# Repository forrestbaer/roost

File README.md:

## Roost keyboard

Based off the Sweep v2.1, added 2mm or so horizontal space, added another set of keys and slots for a fat power switch. Moved battery connectors to the board, moved reset switch so it's easier to get to without being in the way. Larger holes are for mounting these: Mouser part: 575-7305015154727100 for pluggable switches.

Recently added v2 gerbers which use normal Kalih choc hot pluggable sockets as they're MUCH easier and more reliable to solder than the plugs.. Also did a few routing changes but it's otherwise the same board, same config.

Feel free to copy and modify..

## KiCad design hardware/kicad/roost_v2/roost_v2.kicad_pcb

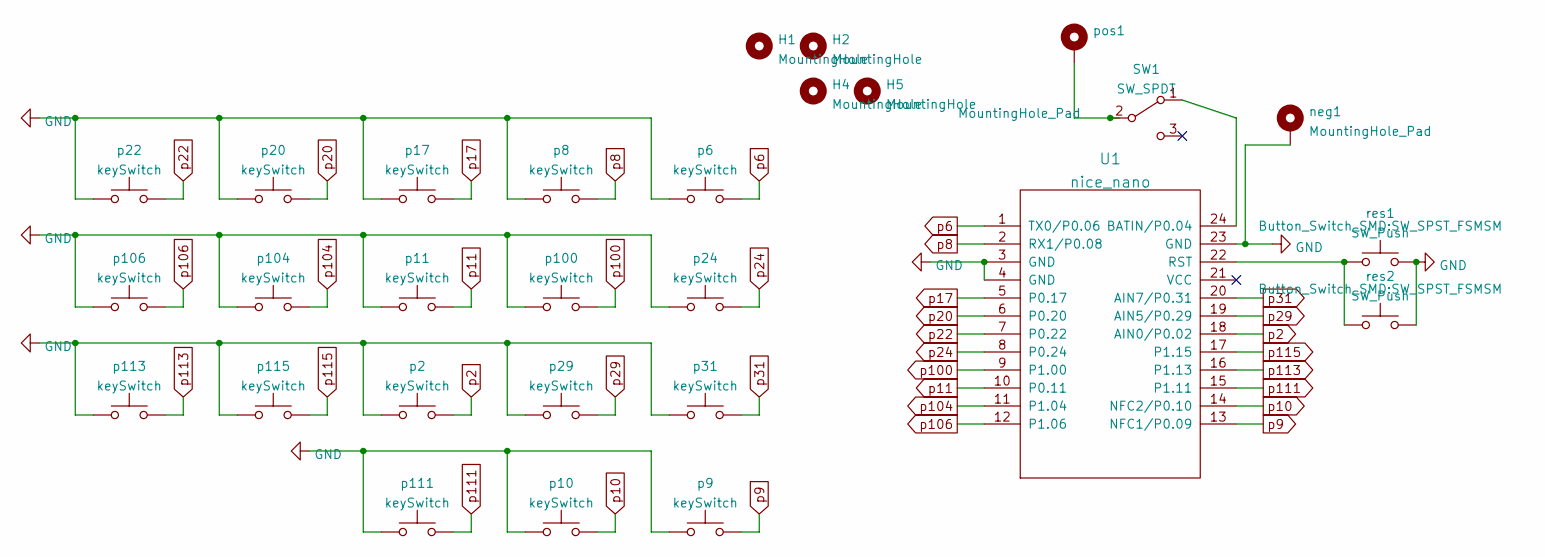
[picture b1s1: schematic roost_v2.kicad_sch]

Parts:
H1, H2, H4, H5: MountingHole; MountingHole_2.2mm_M2
SW1: SW_SPDT; bigswitch
U1: nice_nano
neg1: MountingHole_Pad; MountingHole_2.2mm_M2_DIN965_Pad
p2, p6, p8, p9, p10, p11, p17, p20, p22, p24, p29, p31, p100, p104, p106, p111, p113, p115: keySwitch; Kailh_socket_PG1350_reversible
pos1: MountingHole_Pad; MountingHole_2.2mm_M2_DIN965_Pad
res1, res2: SW_Push; SW_SPST_FSMSM

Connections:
GND: U1.3 (GND), U1.4 (GND), U1.23 (GND), neg1.1, p2.1, p6.1, p8.1, p9.1, p10.1, p11.1, p17.1, p20.1, p22.1, p24.1, p29.1, p31.1, p100.1, p104.1, p106.1, p111.1, p113.1, p115.1, res1.2, res2.2; also elsewhere on the board
unnamed: SW1.1 (A), U1.24 (BATIN/P0.04)
unnamed 2: SW1.2 (B), pos1.1; also elsewhere on the board
unnamed: U1.22 (RST), res1.1, res2.1
p2: U1.18 (AIN0/P0.02), p2.2
p6: U1.1 (TX0/P0.06), p6.2
p8: U1.2 (RX1/P0.08), p8.2
p9: U1.13 (NFC1/P0.09), p9.2
p10: U1.14 (NFC2/P0.10), p10.2
p11: U1.10 (P0.11), p11.2
p17: U1.5 (P0.17), p17.2
p20: U1.6 (P0.20), p20.2
p22: U1.7 (P0.22), p22.2
p24: U1.8 (P0.24), p24.2
p29: U1.19 (AIN5/P0.29), p29.2
p31: U1.20 (AIN7/P0.31), p31.2
p100: U1.9 (P1.00), p100.2
p104: U1.11 (P1.04), p104.2
p106: U1.12 (P1.06), p106.2
p111: U1.15 (P1.11), p111.2
p113: U1.16 (P1.13), p113.2
p115: U1.17 (P1.15), p115.2

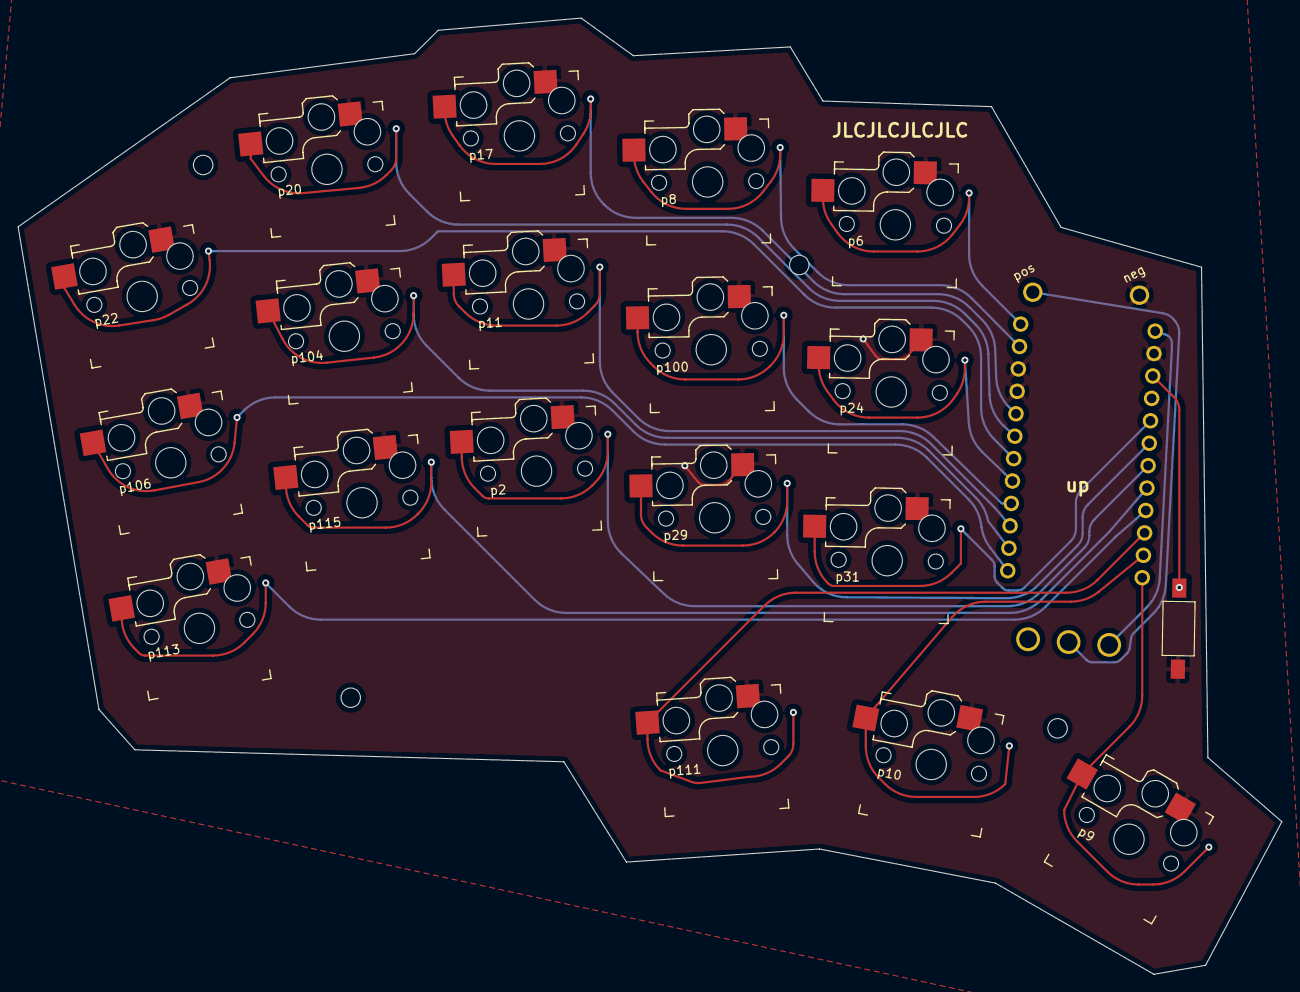
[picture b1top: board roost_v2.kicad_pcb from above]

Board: 2 copper layers, 143.0 x 108.2 mm, 28 parts (1 on the bottom side), 22 nets.

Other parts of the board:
neg: MountingHole_Pad; MountingHole_2.2mm_M2_DIN965_Pad
pos: MountingHole_Pad; MountingHole_2.2mm_M2_DIN965_Pad

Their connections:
GND: neg.1; also elsewhere on the board
unnamed 2: pos.1; also elsewhere on the board

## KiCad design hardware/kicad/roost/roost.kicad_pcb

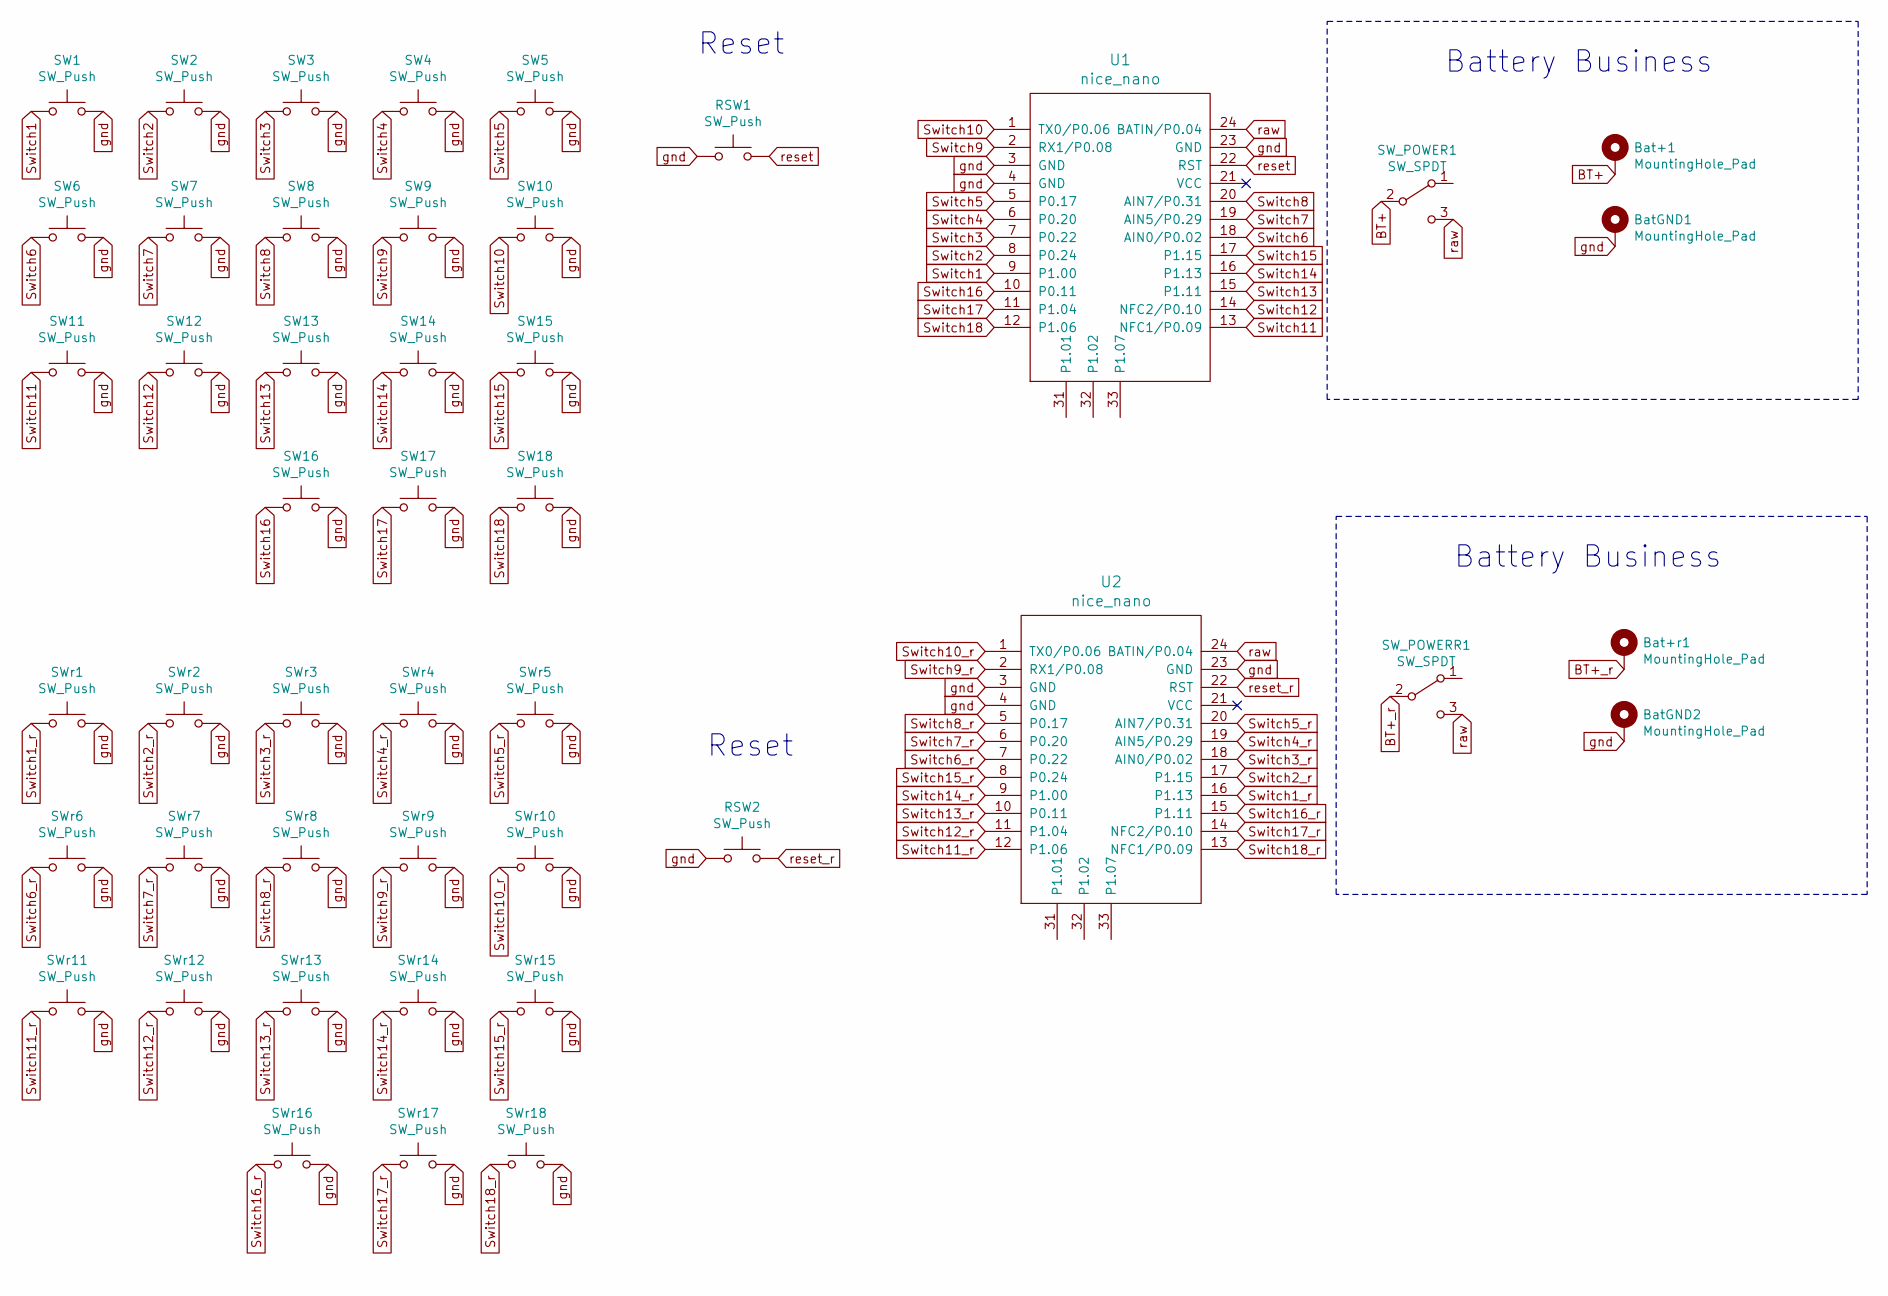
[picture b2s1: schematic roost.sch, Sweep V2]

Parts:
Bat+1: MountingHole_Pad; battery hole
Bat+r1: MountingHole_Pad; battery hole
BatGND1, BatGND2: MountingHole_Pad; battery hole
RSW1, RSW2: SW_Push; SW_SPST_B3U-1000P
SW1, SW2, SW3, SW4, SW5, SW6, SW7, SW8, SW9, SW10, SW11, SW12, SW13, SW14, SW15, SW16, SW17, SW18: SW_Push; SW_Kailh_Choc_V1_1.00u
SW_POWER1: SW_SPDT; bigswitch
SW_POWERR1: SW_SPDT; bigswitch
SWr1, SWr2, SWr3, SWr4, SWr5, SWr6, SWr7, SWr8, SWr9, SWr10, SWr11, SWr12, SWr13, SWr14, SWr15, SWr16, SWr17, SWr18: SW_Push; SW_Kailh_Choc_V1_1.00u
U1, U2: nice_nano

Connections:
BT+: Bat+1.1, SW_POWER1.2 (B); also elsewhere on the board
BT+_r: Bat+r1.1, SW_POWERR1.2 (B); also elsewhere on the board
Switch1: SW1.1, U1.9 (P1.00)
Switch1_r: SWr1.1, U2.16 (P1.13)
Switch2: SW2.1, U1.8 (P0.24)
Switch2_r: SWr2.1, U2.17 (P1.15)
Switch3: SW3.1, U1.7 (P0.22)
Switch3_r: SWr3.1, U2.18 (AIN0/P0.02)
Switch4: SW4.1, U1.6 (P0.20)
Switch4_r: SWr4.1, U2.19 (AIN5/P0.29)
Switch5: SW5.1, U1.5 (P0.17)
Switch5_r: SWr5.1, U2.20 (AIN7/P0.31)
Switch6: SW6.1, U1.18 (AIN0/P0.02)
Switch6_r: SWr6.1, U2.7 (P0.22)
Switch7: SW7.1, U1.19 (AIN5/P0.29)
Switch7_r: SWr7.1, U2.6 (P0.20)
Switch8: SW8.1, U1.20 (AIN7/P0.31)
Switch8_r: SWr8.1, U2.5 (P0.17)
Switch9: SW9.1, U1.2 (RX1/P0.08)
Switch9_r: SWr9.1, U2.2 (RX1/P0.08)
Switch10: SW10.1, U1.1 (TX0/P0.06)
Switch10_r: SWr10.1, U2.1 (TX0/P0.06)
Switch11: SW11.1, U1.13 (NFC1/P0.09)
Switch11_r: SWr11.1, U2.12 (P1.06)
Switch12: SW12.1, U1.14 (NFC2/P0.10)
Switch12_r: SWr12.1, U2.11 (P1.04)
Switch13: SW13.1, U1.15 (P1.11)
Switch13_r: SWr13.1, U2.10 (P0.11)
Switch14: SW14.1, U1.16 (P1.13)
Switch14_r: SWr14.1, U2.9 (P1.00)
Switch15: SW15.1, U1.17 (P1.15)
Switch15_r: SWr15.1, U2.8 (P0.24)
Switch16: SW16.1, U1.10 (P0.11)
Switch16_r: SWr16.1, U2.15 (P1.11)
Switch17: SW17.1, U1.11 (P1.04)
Switch17_r: SWr17.1, U2.14 (NFC2/P0.10)
Switch18: SW18.1, U1.12 (P1.06)
Switch18_r: SWr18.1, U2.13 (NFC1/P0.09)
gnd: BatGND1.1, BatGND2.1, RSW1.1, RSW2.1, SW1.2, SW2.2, SW3.2, SW4.2, SW5.2, SW6.2, SW7.2, SW8.2, SW9.2, SW10.2, SW11.2, SW12.2, SW13.2, SW14.2, SW15.2, SW16.2, SW17.2, SW18.2, SWr1.2, SWr2.2, SWr3.2, SWr4.2, SWr5.2, SWr6.2, SWr7.2, SWr8.2, SWr9.2, SWr10.2, SWr11.2, SWr12.2, SWr13.2, SWr14.2, SWr15.2, SWr16.2, SWr17.2, SWr18.2, U1.3 (GND), U1.4 (GND), U1.23 (GND), U2.3 (GND), U2.4 (GND), U2.23 (GND); also elsewhere on the board
raw: SW_POWER1.3 (C), SW_POWERR1.3 (C), U1.24 (BATIN/P0.04), U2.24 (BATIN/P0.04)
reset: RSW1.2, U1.22 (RST)
reset_r: RSW2.2, U2.22 (RST)

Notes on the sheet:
Battery Business
Reset

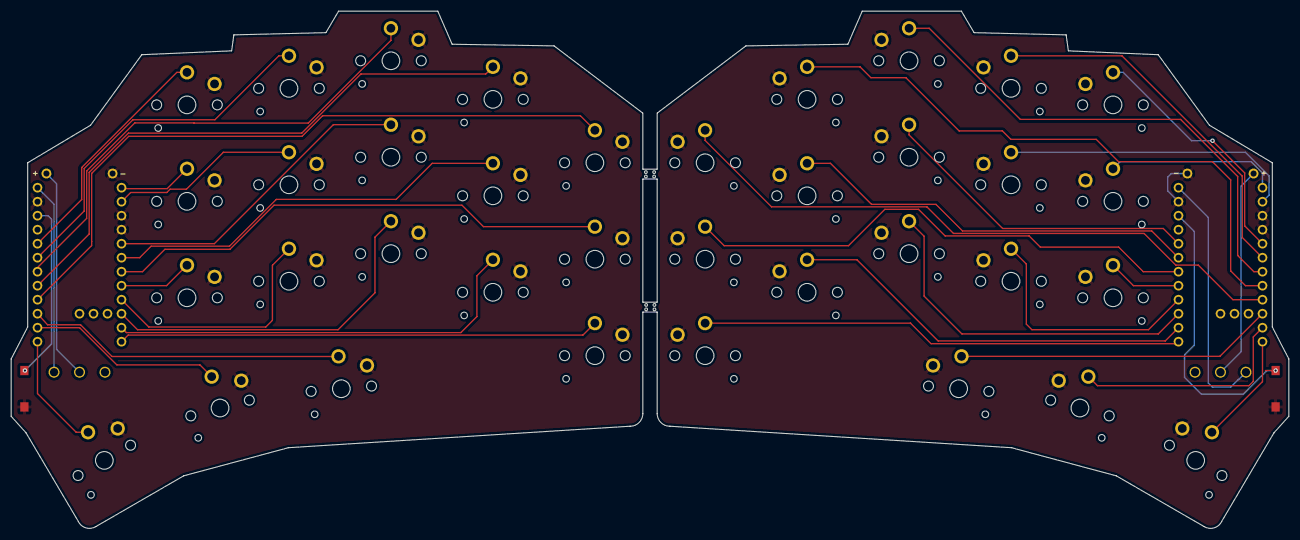
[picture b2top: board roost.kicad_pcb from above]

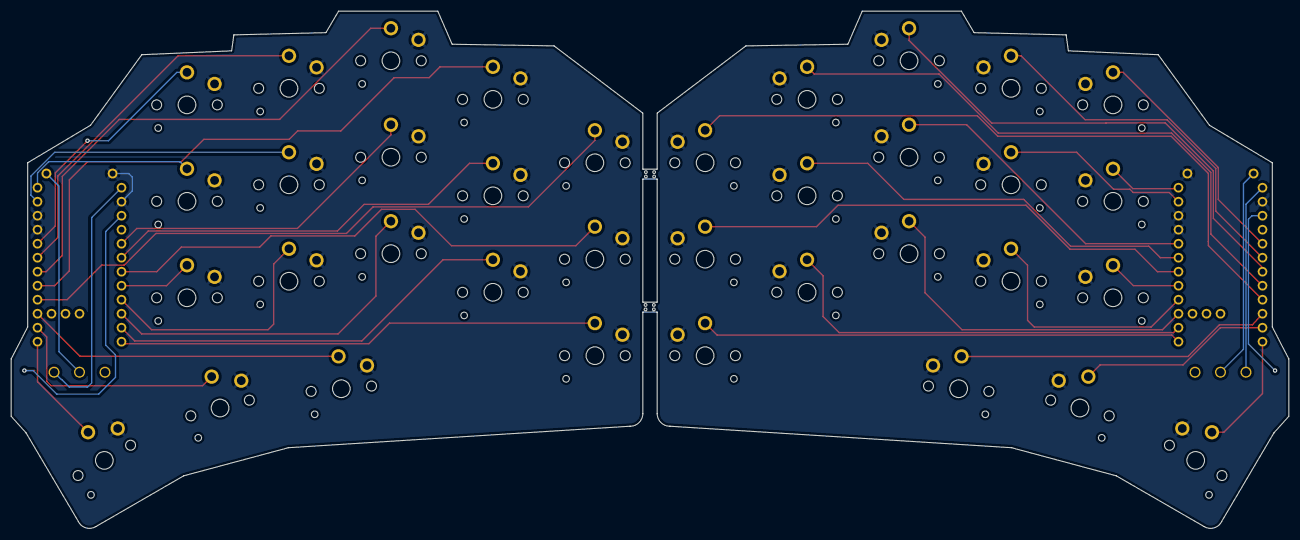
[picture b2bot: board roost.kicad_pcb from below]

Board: 2 copper layers, 231.8 x 93.8 mm, 48 parts (22 on the bottom side), 42 nets.

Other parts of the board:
+: MountingHole_Pad; battery hole
+#2: MountingHole_Pad; battery hole
-: MountingHole_Pad; battery hole
-#2: MountingHole_Pad; battery hole
mouse-bite-2mm-slot, mouse-bite-2mm-slot#2: VAL**; mouse-bite-2mm-slot-with-space-for-track

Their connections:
BT+: +#2.1; also elsewhere on the board
BT+_r: +.1; also elsewhere on the board
gnd: -.1, -#2.1; also elsewhere on the board

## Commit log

2021-12-15 Initial User Config.
2021-12-15 first roost build
2021-12-15 new lefthand io map test
2021-12-15 new lefthand io map test 2
2021-12-15 new righthand io map test
2021-12-15 updated keymap for roost
2021-12-15 trying to fix bluetooth behavior
2021-12-16 better shift placement
2021-12-16 better numpad use
2021-12-16 adding hardware for roost
2021-12-17 swapping shift
2021-12-17 adding kicad files
2021-12-18 keypad mapping
2021-12-21 updating keymap
2022-01-12 keymap updates
2022-01-12 god i hate this syntax
2022-01-12 better number placement?
2022-01-12 ok this will do, one small fix
2022-01-15 fixing numpad
2022-01-15 swap enter in keypad mode
2022-01-15 hopefully fixes strange behavior
2022-01-15 gah can't believe i messed that up
2022-01-17 added v2 first draft
2022-01-29 adding roostv2 definitions
2022-01-29 wrong dtsi
2022-01-29 forgot some files
2022-01-29 updating existing keymap
2022-01-29 Adding a better v2 with option for mountable sockets which seem to work a lot better and are easier to use without accidentally getting solder in the mount holes
2022-02-05 added version 2 with standard kailh choc hotswap sockets which are much more reliable and easy to solder than the plugs
2022-02-25 something wrong with clear link
2022-03-10 removing upper deck
2022-03-10 sick of iit
2022-03-10 adding numbers back
2022-03-10 adding shift back
2022-03-21 v2 notice added
2022-03-23 pagedown where it should be
2022-04-10 latest version + return to something something..
2022-04-10 removing broken thing
2022-04-23 adding audio keys
2022-06-07 adding tmux key
2023-05-28 Configuration updates, bit of formatting cleanup
